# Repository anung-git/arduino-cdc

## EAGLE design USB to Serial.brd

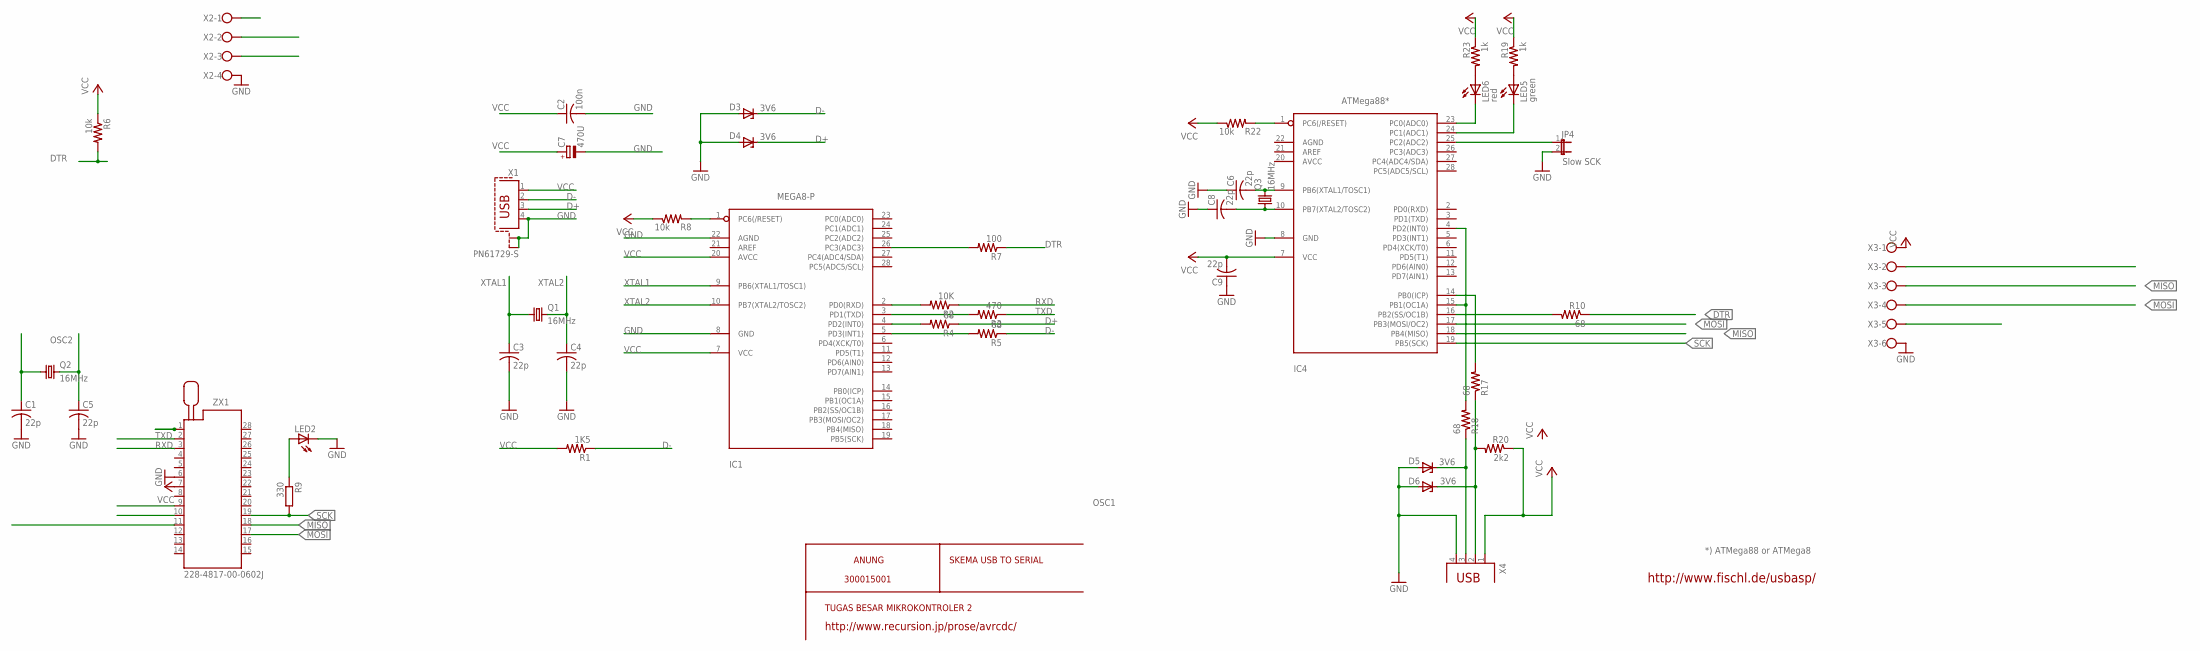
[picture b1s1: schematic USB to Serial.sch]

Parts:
C1, C3, C4, C5, C6, C8, C9: 22p; C050-024X044
C2: 100n; C050-024X044
C7: 470U; E5-5
D3, D4, D5, D6: 3V6; DO34Z7
IC1: MEGA8-P; DIL28-3
IC4: ATMega88*; DIL28-3
JP4: Slow SCK; JP1
LED2: LED5MM
LED5: green; LED5MM
LED6: red; LED5MM
Q1, Q2, Q3: 16MHz; HC49/S
R1: 1K5; 0207/7
R2: 10K; 0207/7
R3: 470; 0207/7
R4, R5: 68; 0207/7
R6: 10k; 0207/7
R7: 100; 0207/7
R8, R22: 10k; 0207/10
R9: 330; 0207/10
R10, R17, R18: 68; 0207/10
R19, R23: 1k; 0207/10
R20: 2k2; 0207/10
X1: PN61729-S
X2: W237-4
X3: W237-6
X4: PN61729
ZX1: 228-4817-00-0602J

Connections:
D+: D4.C, R4.1, X1.3
D-: D3.C, R1.1, R5.1, X1.2
DTR: R6.2, R7.1, R10.1, X2.1, ZX1.1
GND: C1.2, C2.2, C3.2, C4.2, C5.2, C6.1, C7.-, C8.1, C9.1, D3.A, D4.A, D5.A, D6.A, IC1.8 (GND), IC1.22 (AGND), IC4.8 (GND), JP4.2, LED2.K (C), X1.4, X1.S1, X1.S2, X2.4, X3.6, X4.4, ZX1.6
MISO: IC4.18 (PB4(MISO)), X3.3, ZX1.18
MOSI: IC4.17 (PB3(MOSI/OC2)), X3.4, ZX1.17
unnamed: IC4.16 (PB2(SS/OC1B)), R10.2, X3.5
unnamed: IC1.2 (PD0(RXD)), R2.2
unnamed: IC1.3 (PD1(TXD)), R3.2
unnamed: IC1.1 (PC6(/RESET)), R8.2
unnamed: IC1.4 (PD2(INT0)), R4.2
unnamed: IC1.5 (PD3(INT1)), R5.2
unnamed: IC1.26 (PC3(ADC3)), R7.2
unnamed: LED2.A, R9.1
unnamed: D6.C, R17.1, R20.2, X4.2
unnamed: D5.C, R18.1, X4.3
unnamed: C6.2, IC4.9 (PB6(XTAL1/TOSC1)), Q3.2
unnamed: C8.2, IC4.10 (PB7(XTAL2/TOSC2)), Q3.1
unnamed: LED5.A, R19.2
unnamed: IC4.4 (PD2(INT0)), IC4.15 (PB1(OC1A)), R18.2
unnamed: IC4.1 (PC6(/RESET)), R22.2
unnamed: IC4.25 (PC2(ADC2)), JP4.1
unnamed: LED6.A, R23.2
unnamed: IC4.23 (PC0(ADC0)), LED6.K (C)
unnamed: IC4.24 (PC1(ADC1)), LED5.K (C)
unnamed: IC4.14 (PB0(ICP)), R17.2
OSC1: C1.1, Q2.1, ZX1.9
OSC2: C5.1, Q2.2, ZX1.10
RXD: R2.1, X2.3, ZX1.3
SCK: IC4.19 (PB5(SCK)), R9.2, X3.2, ZX1.19
TXD: R3.1, X2.2, ZX1.2
VCC: C2.1, C7.+, C9.2, IC1.7 (VCC), IC1.20 (AVCC), IC4.7 (VCC), R1.2, R6.1, R8.1, R19.1, R20.1, R22.1, R23.1, X1.1, X3.1, X4.1, ZX1.7
XTAL1: C3.1, IC1.9 (PB6(XTAL1/TOSC1)), Q1.1
XTAL2: C4.1, IC1.10 (PB7(XTAL2/TOSC2)), Q1.2

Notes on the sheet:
SKEMA USB TO SERIAL
http://www.recursion.jp/prose/avrcdc/
TUGAS BESAR MIKROKONTROLER 2
ANUNG
300015001
http://www.fischl.de/usbasp/
*) ATMega88 or ATMega8

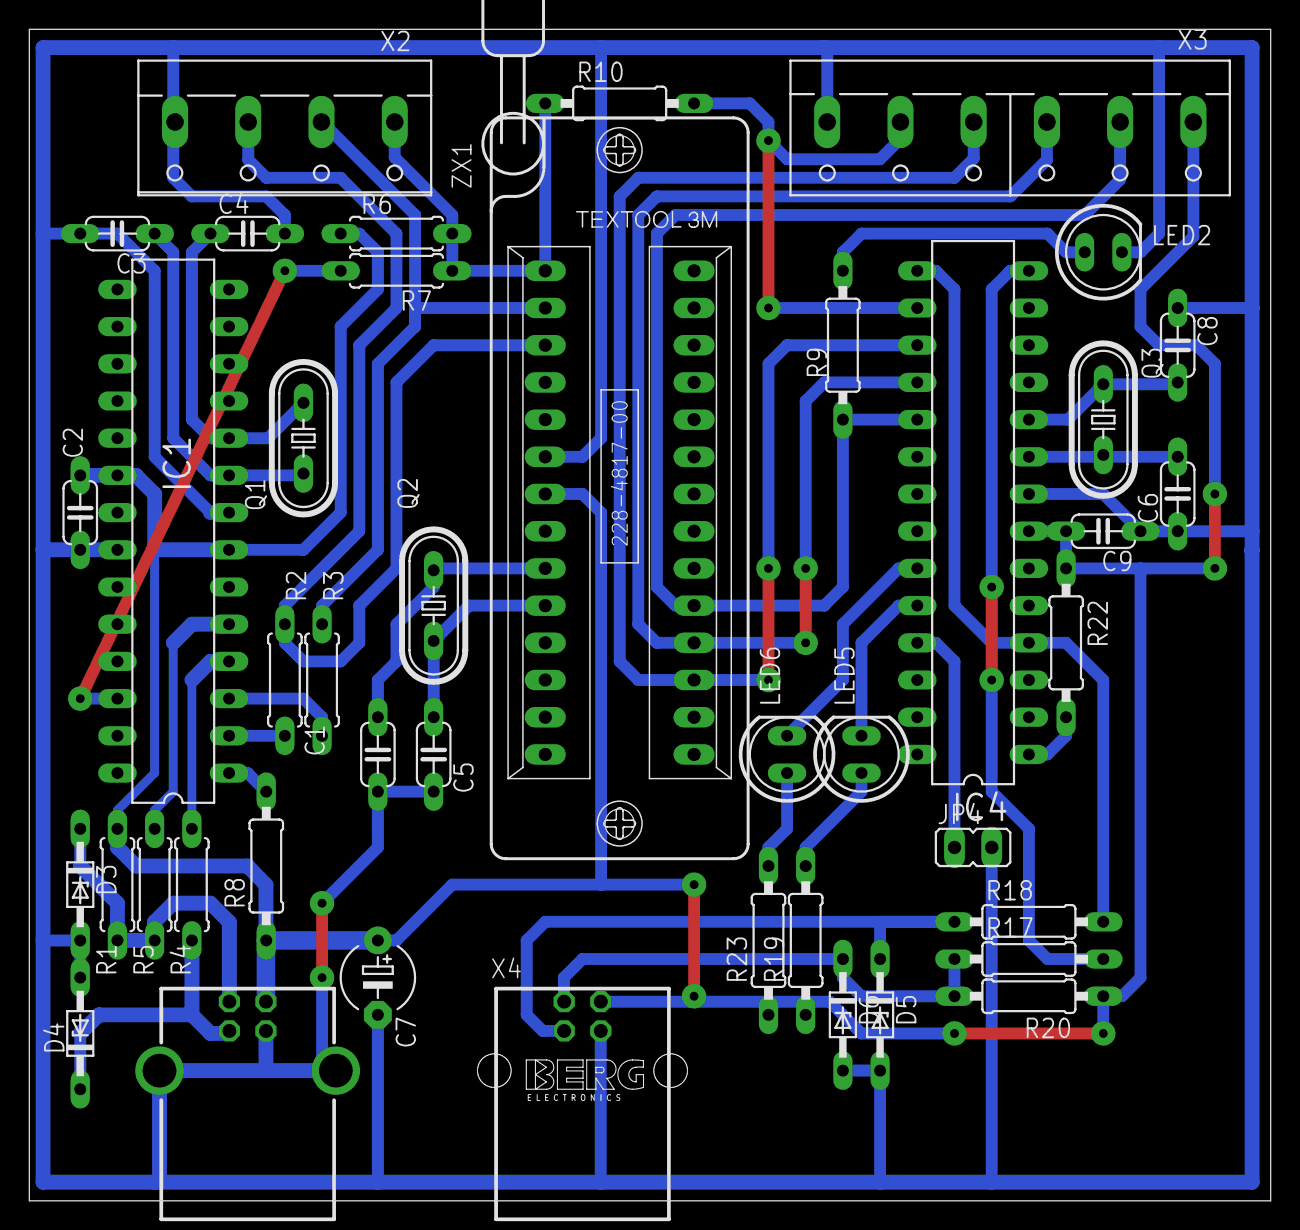
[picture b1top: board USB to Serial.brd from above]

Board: 2 copper layers, 84.8 x 80.0 mm, 43 parts (0 on the bottom side), 34 nets.

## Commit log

2019-09-18 upload
2019-09-19 finish
2019-09-19 upload kamavr
